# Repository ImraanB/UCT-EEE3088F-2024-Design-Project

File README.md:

# UCT-EEE3088F-2024-Design-Project
This is a repository for the UCT EEE3088F 2024 Micro-mouse Project
# Overall Project
This project involves designing a micromouse that will be able to move through a maze.
There are 4 subsystems that work together to form the micromouse:
## The motherboard
(We are given this) Connects all the PCBs together.
## The Processor
(We are given this) Contains an STM32L476 microcontroller. This microcontroller will be used to program different sections and subsystems of the micromouse.
## The Power
Responsible for powering the entire system:
- Run motors and charge battery
- Fit onto pin headers on motherboard
- It will need to be able to be an apporpriate size for balance and space issues
## The Sensor
Resposible for detecting/sensing objects
- Detect objects
- Fit onto pin headers on motherboard
- It will need to be able to be an apporpriate size for balance and space issues

# How this GitHub repo works
There are 2 main folders for the 2 subsystems that need to be designed: Power and Sensing.
Each of these folders contain the relevant documents that are associated with each subsystem

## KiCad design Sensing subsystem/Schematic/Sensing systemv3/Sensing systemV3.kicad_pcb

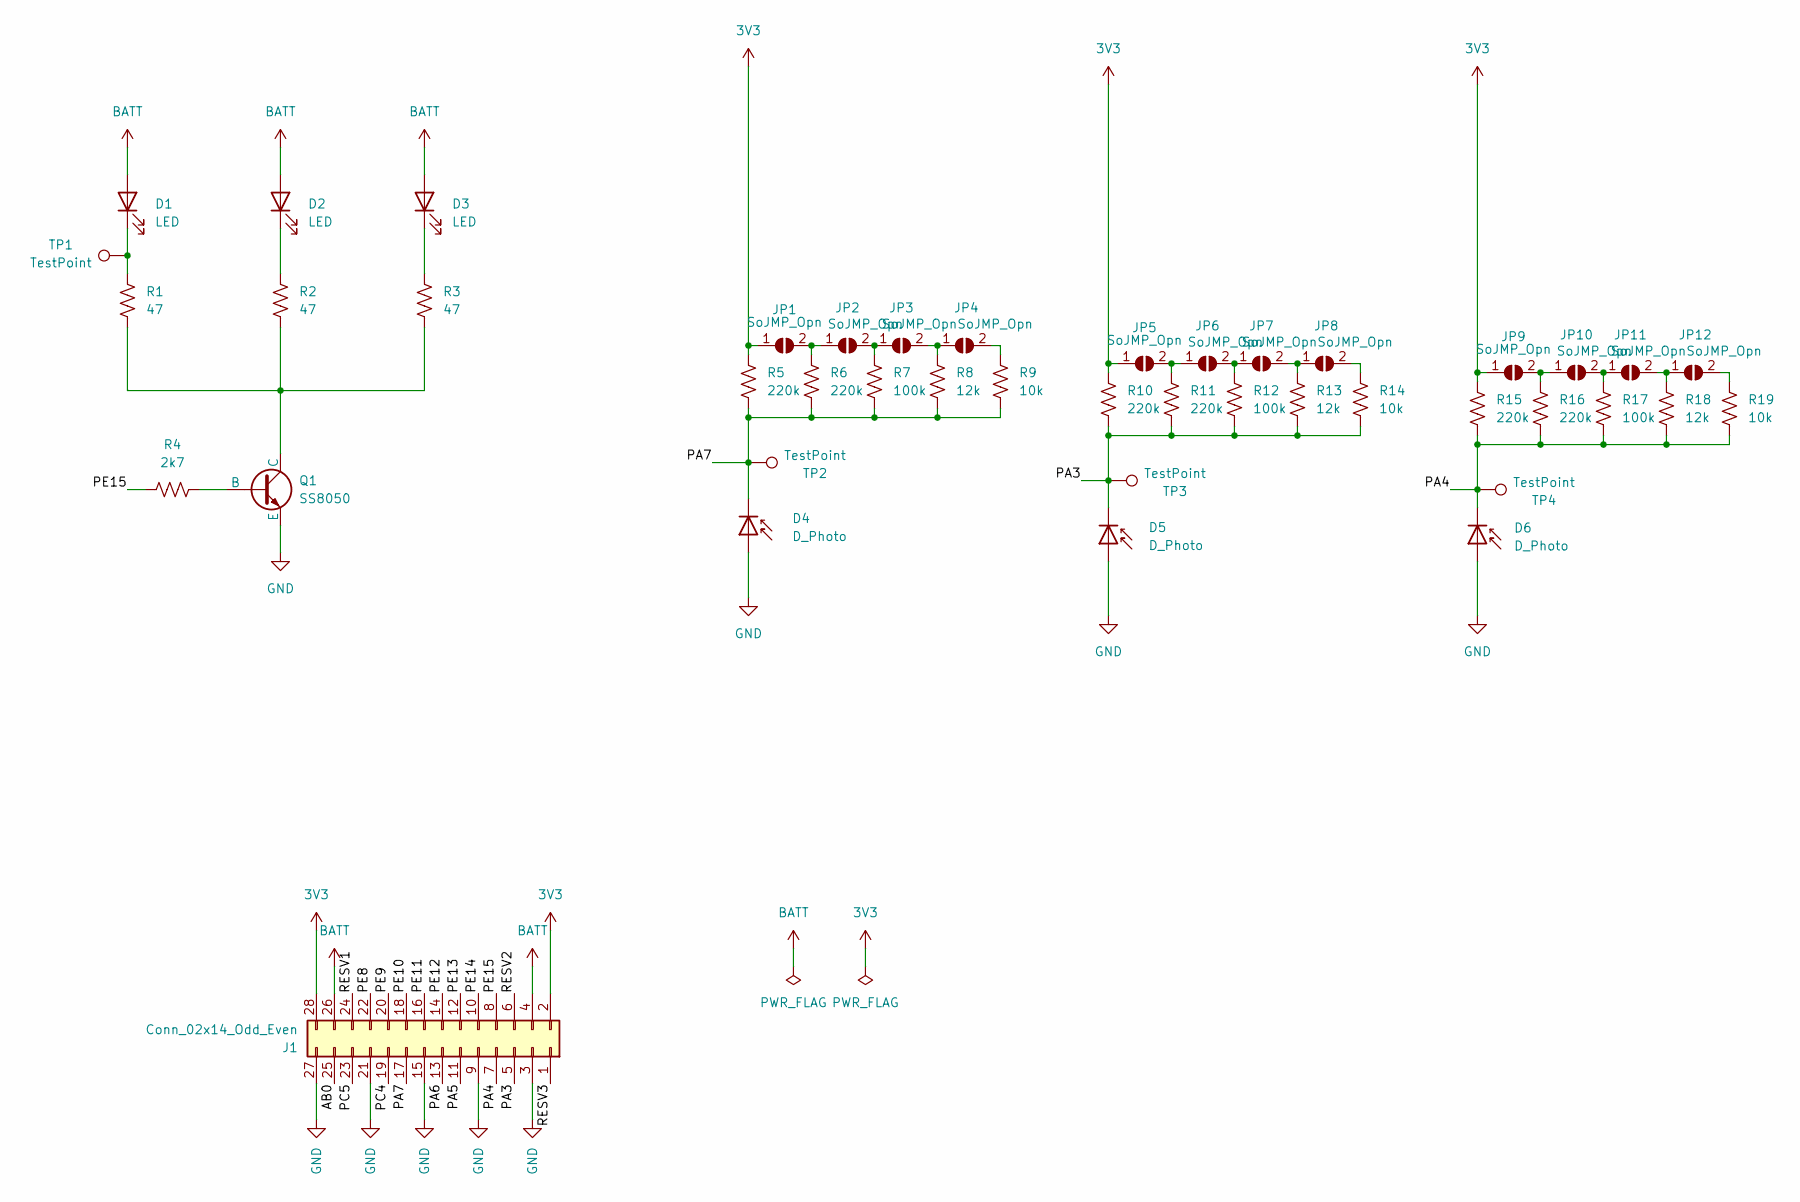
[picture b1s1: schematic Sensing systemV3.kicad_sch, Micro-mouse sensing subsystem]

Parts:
D1, D2, D3: LED; LED_D5.0mm_Horizontal_O1.27mm_Z3.0mm_Clear; LCSC C405270
D4, D5, D6: D_Photo; LED_D5.0mm_Horizontal_O1.27mm_Z3.0mm_Clear; LCSC C95399
J1: Conn_02x14_Odd_Even; PinHeader_2x14_P2.54mm_Vertical
JP1, JP2, JP3, JP4, JP5, JP6, JP7, JP8, JP9, JP10, JP11, JP12: SoJMP_Opn; SolderJumper-2_P1.3mm_Open_RoundedPad1.0x1.5mm
Q1: SS8050; SOT-23-3; LCSC C2150
R1, R2, R3: 47; R_0805_2012Metric; LCSC C17714
R4: 2k7; R_0805_2012Metric; LCSC C17530
R5, R6, R10, R11, R15, R16: 220k; R_0805_2012Metric; LCSC C17556
R7, R12, R17: 100k; R_0805_2012Metric; LCSC C149504
R8, R13, R18: 12k; R_0805_2012Metric; LCSC C17444
R9, R14, R19: 10k; R_0805_2012Metric; LCSC C17414
TP1, TP2, TP3, TP4: TestPoint; TestPoint_Pad_2.0x2.0mm

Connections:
3V3: J1.2, J1.28, JP1.1 (A), JP5.1 (A), JP9.1 (A), R5.1, R10.1, R15.1
/AB0: J1.25
/PA3: D5.1 (K), J1.5, R10.2, R11.2, R12.2, R13.2, R14.2, TP3.1
/PA4: D6.1 (K), J1.7, R15.2, R16.2, R17.2, R18.2, R19.2, TP4.1
/PA5: J1.11
/PA6: J1.13
/PA7: D4.1 (K), J1.17, R5.2, R6.2, R7.2, R8.2, R9.2, TP2.1
/PC4: J1.19
/PC5: J1.23
/PE8: J1.22
/PE9: J1.20
/PE10: J1.18
/PE11: J1.16
/PE12: J1.14
/PE13: J1.12
/PE14: J1.10
/PE15: J1.8, R4.1
/RESV1: J1.24
/RESV2: J1.6
/RESV3: J1.1
BATT: D1.2 (A), D2.2 (A), D3.2 (A), J1.4, J1.26
GND: D4.2 (A), D5.2 (A), D6.2 (A), J1.3, J1.9, J1.15, J1.21, J1.27, Q1.3 (E)
unnamed: D1.1 (K), R1.1, TP1.1
unnamed: D2.1 (K), R2.1
unnamed: D3.1 (K), R3.1
unnamed: JP1.2 (B), JP2.1 (A), R6.1
unnamed: JP2.2 (B), JP3.1 (A), R7.1
unnamed: JP3.2 (B), JP4.1 (A), R8.1
unnamed: JP4.2 (B), R9.1
unnamed: JP5.2 (B), JP6.1 (A), R11.1
unnamed: JP6.2 (B), JP7.1 (A), R12.1
unnamed: JP7.2 (B), JP8.1 (A), R13.1
unnamed: JP8.2 (B), R14.1
unnamed: JP9.2 (B), JP10.1 (A), R16.1
unnamed: JP10.2 (B), JP11.1 (A), R17.1
unnamed: JP11.2 (B), JP12.1 (A), R18.1
unnamed: JP12.2 (B), R19.1
unnamed: Q1.2 (B), R4.2
unnamed: Q1.1 (C), R1.2, R2.2, R3.2

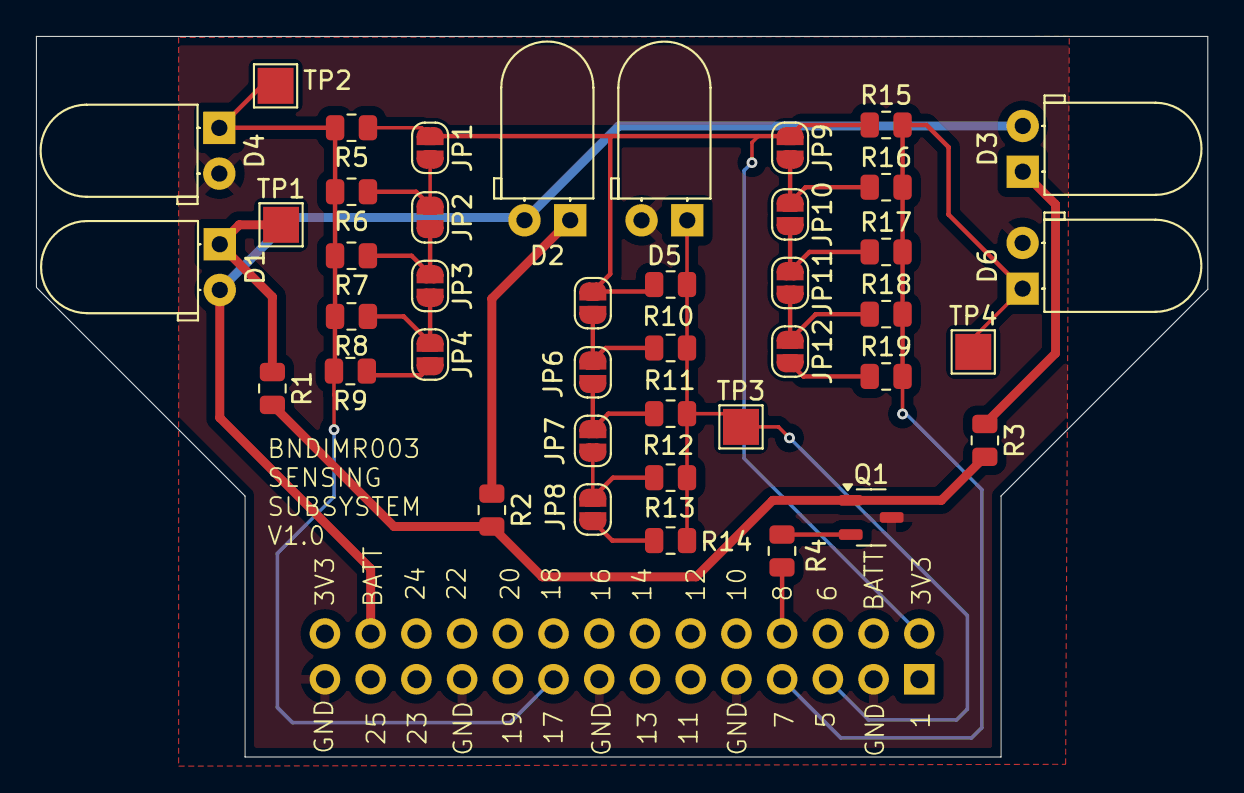
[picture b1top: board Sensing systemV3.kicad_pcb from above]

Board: 2 copper layers, 65.1 x 40.0 mm, 43 parts (1 on the bottom side), 24 nets.

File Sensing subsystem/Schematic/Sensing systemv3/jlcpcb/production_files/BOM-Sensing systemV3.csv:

Comment,Designator,Footprint,LCSC
100k,"R12,R17,R7",R_0805_2012Metric,C149504
10k,"R14,R19,R9",R_0805_2012Metric,C17414
12k,"R13,R18,R8",R_0805_2012Metric,C17444
2k7,R4,R_0805_2012Metric,C17530
220k,"R10,R11,R15,R16,R5,R6",R_0805_2012Metric,C17556
47,"R1,R2,R3",R_0805_2012Metric,C17714
SS8050,Q1,SOT-23-3,C2150
LED,"D1,D2,D3",LED_D5.0mm_Horizontal_O1.27mm_Z3.0mm_Clear,C405270
D_Photo,"D4,D5,D6",LED_D5.0mm_Horizontal_O1.27mm_Z3.0mm_Clear,C95399

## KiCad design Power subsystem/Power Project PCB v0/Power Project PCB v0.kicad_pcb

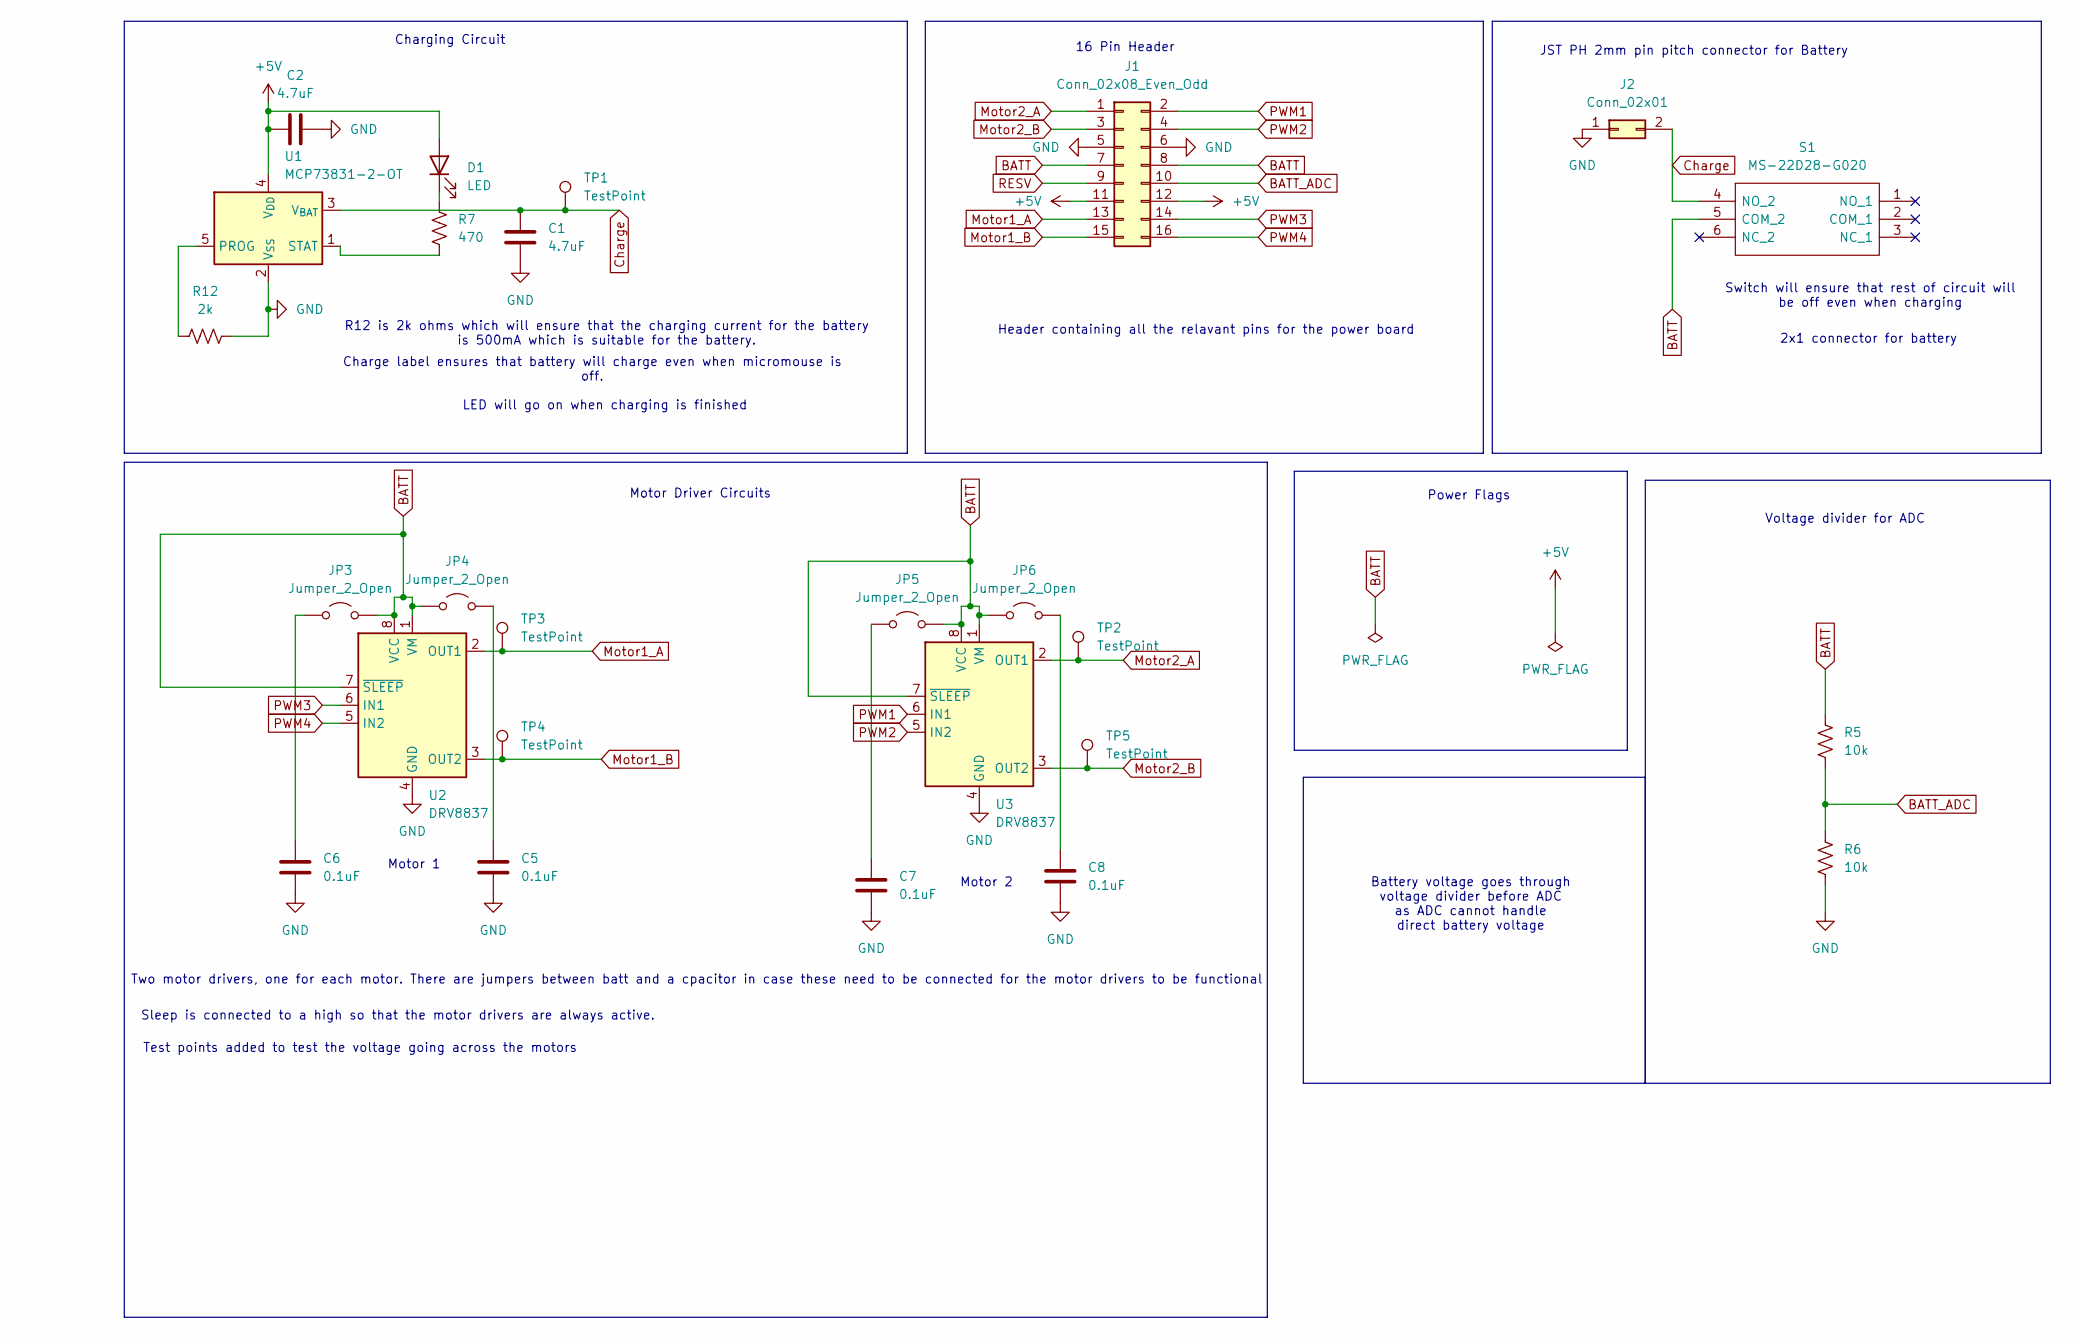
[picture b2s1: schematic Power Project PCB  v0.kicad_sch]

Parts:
C1, C2: 4.7uF; C_0805_2012Metric; LCSC C1779
C5, C6, C7, C8: 0.1uF; C_0805_2012Metric; LCSC C1779
D1: LED; LED_0805_2012Metric; LCSC C84256
J1: Conn_02x08_Even_Odd; PinHeader_2x08_P2.54mm_Vertical
J2: Conn_02x01; PinHeader_2x01_P2.00mm_Vertical
JP3, JP4, JP5, JP6: Jumper_2_Open; SolderJumper-2_P1.3mm_Open_RoundedPad1.0x1.5mm
R5, R6: 10k; R_0805_2012Metric; LCSC C17414
R7: 470; R_0805_2012Metric; LCSC C17710
R12: 2k; R_0805_2012Metric; LCSC C17604
S1: MS-22D28-G020; MS22D28G020; Manufacturer_Part_Number MS-22D28-G020; LCSC C963205
TP1, TP2, TP3, TP4, TP5: TestPoint; TestPoint_Keystone_5019_Minature
U1: MCP73831-2-OT; SOT-23-5; LCSC C424093
U2, U3: DRV8837; WSON-8-1EP_2x2mm_P0.5mm_EP0.9x1.6mm; LCSC C39159

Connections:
+5V: C2.1, D1.2 (A), J1.11, J1.12, U1.4 (V_{DD})
BATT: J1.7, J1.8, JP3.2 (B), JP4.1 (A), JP5.2 (B), JP6.1 (A), R5.1, S1.5 (COM_2), U2.1 (VM), U2.7 (~SLEEP), U2.8 (VCC), U3.1 (VM), U3.7 (~SLEEP), U3.8 (VCC)
BATT_ADC: J1.10, R5.2, R6.1
Charge: C1.1, J2.2, S1.4 (NO_2), TP1.1, U1.3 (V_{BAT})
GND: C1.2, C2.2, C5.1, C6.1, C7.1, C8.1, J1.5, J1.6, J2.1, R6.2, R12.1, U1.2 (V_{SS}), U2.4 (GND), U2.9 (GND), U3.4 (GND), U3.9 (GND)
Motor1_A: J1.13, TP3.1, U2.2 (OUT1)
Motor1_B: J1.15, TP4.1, U2.3 (OUT2)
Motor2_A: J1.1, TP2.1, U3.2 (OUT1)
Motor2_B: J1.3, TP5.1, U3.3 (OUT2)
unnamed: D1.1 (K), R7.1
unnamed: C6.2, JP3.1 (A)
unnamed: C5.2, JP4.2 (B)
unnamed: C7.2, JP5.1 (A)
unnamed: C8.2, JP6.2 (B)
unnamed: R12.2, U1.5 (PROG)
unnamed: R7.2, U1.1 (STAT)
PWM1: J1.2, U3.6 (IN1)
PWM2: J1.4, U3.5 (IN2)
PWM3: J1.14, U2.6 (IN1)
PWM4: J1.16, U2.5 (IN2)
RESV: J1.9

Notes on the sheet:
Motor 1
Battery voltage goes through voltage divider before ADC as ADC cannot handle direct battery voltage
Switch will ensure that rest of circuit will be off even when charging
Header containing all the relavant pins for the power board
Charging Circuit
Charge label ensures that battery will charge even when micromouse is off.
Motor 2
Sleep is connected to a high so that the motor drivers are always active.
16 Pin Header
LED will go on when charging is finished
R12 is 2k ohms which will ensure that the charging current for the battery is 500mA which is suitable for the battery.
Test points added to test the voltage going across the motors
Two motor drivers, one for each motor. There are jumpers between batt and a cpacitor in case these need to be connected for the motor drivers to be functional
JST PH 2mm pin pitch connector for Battery
2x1 connector for battery
Motor Driver Circuits
Voltage divider for ADC
Power Flags

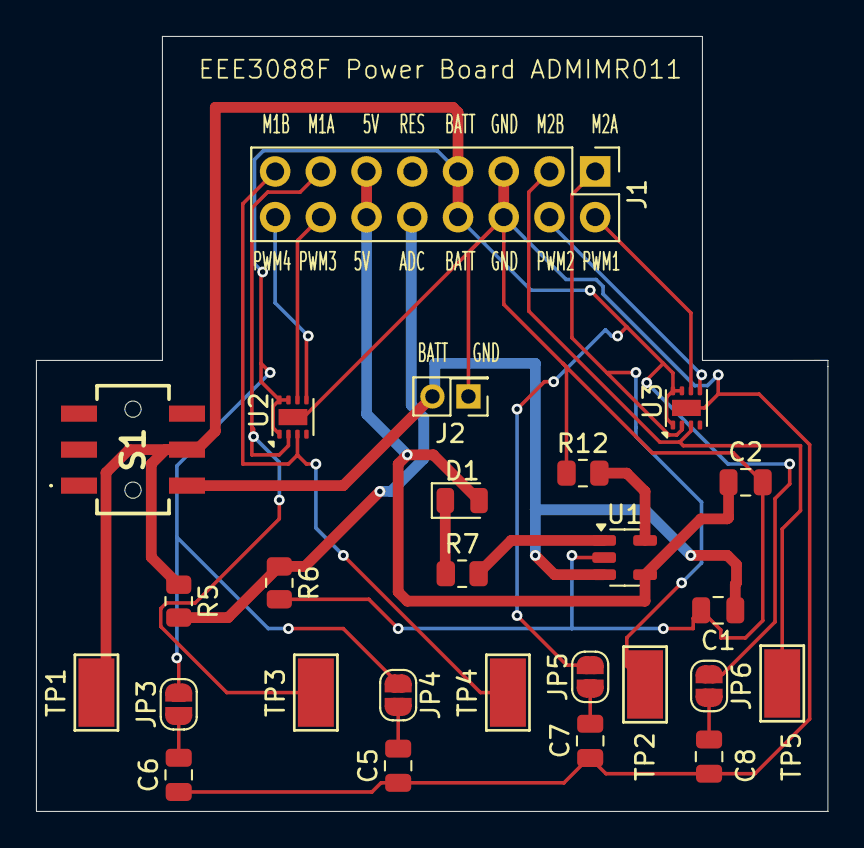
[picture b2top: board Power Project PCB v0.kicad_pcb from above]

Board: 2 copper layers, 44.0 x 43.1 mm, 26 parts (0 on the bottom side), 20 nets.

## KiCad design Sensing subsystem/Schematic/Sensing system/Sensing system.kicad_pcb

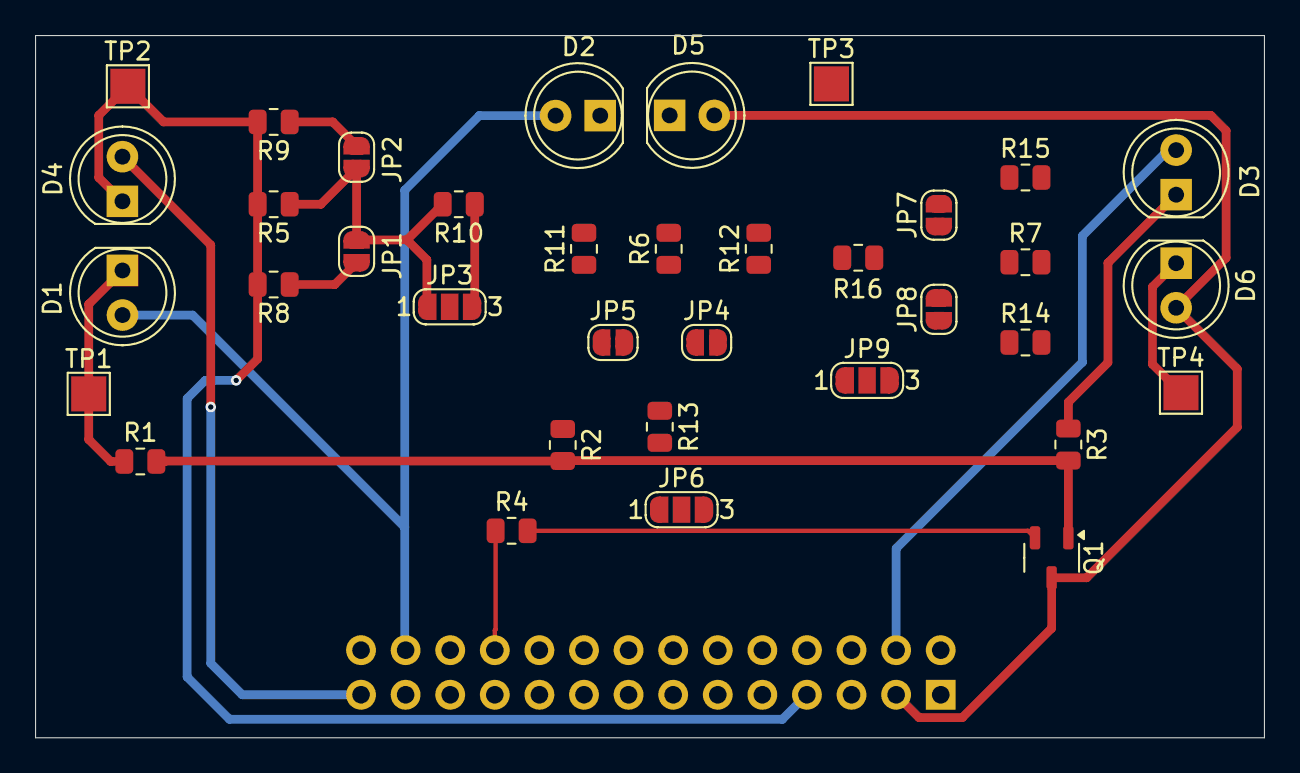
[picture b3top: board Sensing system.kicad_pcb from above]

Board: 2 copper layers, 70.0 x 40.0 mm, 37 parts (1 on the bottom side), 24 nets.

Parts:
D1, D2, D3: LED; LED_D5.0mm
D4, D5, D6: D_Photo; LED_D5.0mm
J1: Conn_02x14_Odd_Even; PinHeader_2x14_P2.54mm_Vertical
JP1, JP2, JP4, JP5, JP7, JP8: SoJMP_Opn; SolderJumper-2_P1.3mm_Open_RoundedPad1.0x1.5mm
JP3, JP6, JP9: SoJMP_Opn3; SolderJumper-3_P1.3mm_Open_RoundedPad1.0x1.5mm_NumberLabels
Q1: SS8050; SOT-23-3
R1, R2, R3: 47; R_0805_2012Metric
R4: 2k7; R_0805_2012Metric
R5, R6, R7, R8, R9, R11, R12, R14, R15: 10k; R_0805_2012Metric
R10, R13, R16: 100k; R_0805_2012Metric
TP1, TP2, TP3, TP4: TestPoint; TestPoint_Pad_2.0x2.0mm

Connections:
3V3: J1.2, J1.28, JP3.2 (C), JP6.2 (C), JP9.2 (C)
/PA4: D4.1 (K), J1.7, R5.2, R8.2, R9.2, TP2.1
/PA5: D5.1 (K), J1.11, R6.2, R11.2, R12.2, TP3.1
/PA6: D6.1 (K), J1.13, R7.2, R14.2, R15.2, TP4.1
/PE8: J1.22, R4.1
BATT: D1.2 (A), D2.2 (A), D3.2 (A), J1.4, J1.26
GND: D4.2 (A), D5.2 (A), D6.2 (A), J1.3, J1.9, J1.15, J1.21, J1.27, Q1.3 (E)
unnamed: D1.1 (K), R1.1, TP1.1
unnamed: D2.1 (K), R2.1
unnamed: D3.1 (K), R3.1
unnamed: JP1.1 (A), R8.1
unnamed: JP1.2 (B), JP2.1 (A), JP3.1 (A), R5.1, R10.2
unnamed: JP2.2 (B), R9.1
unnamed: JP3.3 (B), R10.1
unnamed: JP4.1 (A), JP5.2 (B), JP6.1 (A), R6.1, R13.2
unnamed: JP4.2 (B), R12.1
unnamed: JP5.1 (A), R11.1
unnamed: JP6.3 (B), R13.1
unnamed: JP7.1 (A), JP8.2 (B), JP9.1 (A), R7.1, R16.2
unnamed: JP7.2 (B), R15.1
unnamed: JP8.1 (A), R14.1
unnamed: JP9.3 (B), R16.1
unnamed: Q1.2 (B), R4.2
unnamed: Q1.1 (C), R1.2, R2.2, R3.2

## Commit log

2024-03-17 Initial structure added
2024-03-17 Add files via upload
    Data Sheet for Battery Charge controller
2024-03-17 Create Understadning project
2024-03-17 Update Understadning project
2024-03-17 Rename Understadning project to Understanding project
2024-03-17 Rename Understanding project to Report questions
2024-03-21 Additional datasheets
2024-03-21 Shematics
2024-03-21 Parts collection
2024-03-21 Schematics
2024-03-24 Sensing system
2024-03-25 Schematic
2024-04-15 Added datasheets that were read through
    Not necessarily all of them used
2024-04-15 PCB and schematic kicad files
2024-04-20 Added some pictures for design plans
2024-04-20 pictures added to design plans
2024-04-21 Datasheets
2024-04-21 Images
2024-04-21 Removal of parts
2024-04-21 pictures
2024-05-17 Added photos of testing
2024-05-17 Test code
2024-05-17 edited names
